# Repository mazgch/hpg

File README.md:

#  mazg.ch - HPG Solution

>**Note** This is a private project from [@mazgch](https://github.com/mazgch) <br> This code and hardware was developped during my free time. [u-blox](https://www.u-blox.com) decided to launch a simliar, inspired product under the name [XPLR-HPG-2](https://www.u-blox.com/en/product/xplr-hpg-2) along with production grade software based on [ubxlib](https://github.com/u-blox/ubxlib). u-blox has published the [hardware](https://github.com/u-blox/XPLR-HPG-hardware) and [software](https://github.com/u-blox/XPLR-HPG-software) on the [u-blox github account](https://github.com/u-blox). You can easily recognize the u-blox productized version by its green PCB color and u-blox sticker and silk logo on the back of the PCB.<br>
<br>
The Arduino software of this project can be compiled for the XPLR-HPG-2/1 by adjusting the `HW_TARGET` defines to `UBLOX_XPLR_HPG2_C214` in the [`software\HW.h`](./software/HW.h) file and selecting the right module/board. 

This project has the goal to demonstrate a high precision positioning function. It uses a Global Navigation Satellite System (GNSS) L1/L2 receiver with Real Time Kinematic (RTK) and Inertial Measurement Unit (IMU) Sensor based Dead Reckoning (DR) function to determine its location. In order achieve its best accuracy the receiver needs a correction data stream. On this solution the correction data can be received from a satellite broadcast using a LBAND receiver or over IP connectivity using Wi-FI or LTE. While other systems typically use local reference stations as correction source that have to be setup a maintained, this system makes use of a continental wide commercial SSR service. The whole solution shared in this project consist of three parts: 

## The three elements of the HPG Solution 

| [**HPG Hardware**](./hardware) | [**HPG Software**](./software) | [**HPG Monitor Webpage**](./monitor) |
|----------|----------|---------|
|  |  |  |
| The HPG hardware has a GNSS and a LBAND receiver that are used to achieve cm-Level precision. A Wi-Fi/BT module and a LTE modem make sure that the board is always connected to the internet. A USB port is used for changing or connecting a powerful host. The CPU of the Wi-Fi/BT module can be programmed with the HPG Software. | The HPG software implements a captive portal for configuration and monitoring. The software operates autonomously, configures all the modules and handles the different correction data sources and provides its data to the RTK system. It can also record two logfiles to the SD card of the GNSS/LBAND and the LTE communication. | The online HPG Monitor webpage at [hpg.mazg.ch](http://hpg.mazg.ch) is a online tools that allows you visualize the data of the solution. You can plot graph, export data to Excel or other offline tools. Satellite information as well as a map overlay are even available. The different messages and commands can be analyzed in a console. A simpler version can be accessed in the captive portal directly. |  

## Getting started

To make this device work as intended you need some accessories like LTE and GNSS antennas, a mobile data plan and nano SIM card and a subscription to PointPerfect. Follow this sequence to get the device configured and setup, click on the image below for a short YouTube video on how to do some of these steps.

1. Insert a nano SIM card, the socket is a push/push socket so don't try to just pull the card out.
2. Optional: Insert a micro-SD card (FAT, max 32GB) if you like the device to record logfiles. 
3. Attach the two LTE antennas to the SMA ports located on the long edges. To avoid mechanical stress on the center pin, make sure you do not rotate the antenna itself but only the nut of the SMA connector. 
4. Connect a survey grade L1/L2/L5 GNSS and LBAND antenna to the SMA port on the small edge of the device and place the antenna in a location with very good and unobstructed visibility to the sky. This is important to allow reliable LBAND reception as well as avoid multipath errors on the GNSS measurements 
5. Connect a USB cable to a computer, this will turn the device on, and you will see various LEDS turn on. In addition, your computer will enumerate several USB devices and serial as well a modem ports will become available.  

6. Optional: if the [software](./software) is not yet programmed, follow the build instructions of the Arduino based software and load it to the device. 
7. In order to add the device to your local Wi-Fi connect your computer or mobile phone with the `hpg-XXXXXX` Wi-Fi network. You will be directed to a captive portal where you can then enter your networks Wi-Fi credentials. Make sure that the Wi-Fi network that you like to connect to is supporting 2.4GHz band. Once done the device will connect to your local network and get an IP. You may want to reset your device to force a fast reconnection.
8. After the device is connected, you can try to connect to it using its host name `hpg-XXXXXX`. The IP address of the device is also reported in the debug output on the console output CDC port at 115'200 baud. A third option is to use the device discovery of the [HPG Monitor](http://hpg.mazg.ch). Some networks do not allow communication between attached Wi-Fi clients so it may be better to connect the device to your computer or mobile in hotspot mode. 
9. After you have successfully connected your device, you need to configure the PointPerfect location device token that you can get from the Thingstream portal and set the possible correction sources to use. If you do not have a device profile, create one with following settings: ``Status = enabled, Auto Activate Devices = true, Hardware Code = mandatory`` Return existing device details if Hardware Code is in use. You can also set the SIM pin, but it is often easier to remove the SIM pin from your SIM card with a mobile phone first. Alternatively you can provide the ``u-centerConfig.json`` to the device.  
10. After that the device will provision the credentials using zero touch provisioning (ZTP) from the PointPerfect servers.
11. Now you are ready to Monitor the operation of the device using the console output on the CDC, using the Monitor webpage that is served directly by the device.

11. You can also access and find your hpg devices using the HPG Monitor webpage at [hpg.mazg.ch](http://hpa.mazg.ch) This webpage displays various status information, messages and can even plot graphs of parameter or satellite signal strenghs. A map overlay completes the functionality of the HPG Monitor. You can even export your data a text, in common file formats for offline tools.
12. You are now ready to start experimenting with this exciting technology and go outside and test RTK positioning in your use cases. The solution is suitable for a variety of applications from Lawn Mower, Heavy machine and Construction vehicles, Drones, Precision Agriculture, Cars and of course Mobile Robotics. 
13. To get best performance sure that the GNSS/LBAND antenna is well positioned and has good visibility to the sky!
14. So have fun and put this solution on your robot, [vehicle](docu/Vehicle.md), [scooter](docu/Scooter.md) or [lawn mower](docu/Mower.md) project. Feel free to connect with me even if it’s just to share the projects you are building using this exciting technology and solution.

## Quick Reference Card

## An all [u-blox](https://www.u-blox.com) solution

This solution is an attempt to design a 'full u-blox solution' using various products In particular the solution implements following hardware and services:

| u-blox Product / Service | Description |
|:--------------:|-----------------------|
| [NINA-W106](https://www.u-blox.com/en/product/nina-w10-series-open-cpu) | An ESP32 based WIFI and BT module with Open CPU that will host the application.     | 
| [LARA-R6001D](https://www.u-blox.com/en/product/lara-r6-series) | A LTE Cat 1 cellular modem with 2G / 3G fallback. |
| [ZED-F9R](https://www.u-blox.com/en/product/zed-f9r-module) | A GNSS Module with RTK, DR and L1/L2 multiband capability. |
| [NEO-D9S](https://www.u-blox.com/en/product/neo-d9s-series) | A LBAND receiver to get PointPerfect correction service. | 
| [ANN-MB](https://www.u-blox.com/en/product/ann-mb-series) | L1/L2 multi-band, high precision GNSS antenna (LBAND is not offically supported, it may work but there is a slight degradation depending on the frequency) | 
| [PointPerfect](https://www.u-blox.com/en/product/pointperfect) | A continental wide SSR correction service with coverage in Europe and North America. |
| [AssistNow](https://www.u-blox.com/en/product/assistnow) | A assisted GNSS services that allows to speed up the system start. |

The hardware allows different SKUs and can be assembled with alternative modules with compatible form-factors such as [SARA-R510S](https://www.u-blox.com/en/product/sara-r5-series), [LENA-R8001](https://www.u-blox.com/en/product/lena-r8-series), [ZED-F9P](https://www.u-blox.com/en/product/zed-f9p-module) or [NEO-D9C](https://www.u-blox.com/en/product/neo-d9c-series).

## Availability

As this is a private project, availability of real prototypes and hardware is pretty much limited to friends and colleagues. I am sharing here my work with the open source community with the goal that others can learn from it and collaborate. If you like to have a discussion or business interesst you can contact me with a DM.

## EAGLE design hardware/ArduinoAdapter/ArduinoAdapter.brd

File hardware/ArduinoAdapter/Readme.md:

# Arduino Adapter Board

This is an adapter for replacing the ArduSimple board in the [Open Mower project](https://github.com/ClemensElflein/OpenMower) by [Clemens Elflein](https://github.com/ClemensElflein/OpenMower/commits?author=ClemensElflein) with this project or a XPLR-HPG-2.

**Remarks**
- The Yellow marked pin headers are mounted on bottom side to provide connection to the Open Mower board.
- The Purple marked pin headers are mounted on top side and connect to the HPG board.
- All other pin header signals are not connected, but can be mounted for mechanical stability. 
- When powering the board in this way do not connect a battery as this is used to inject supply from the Open mower board.

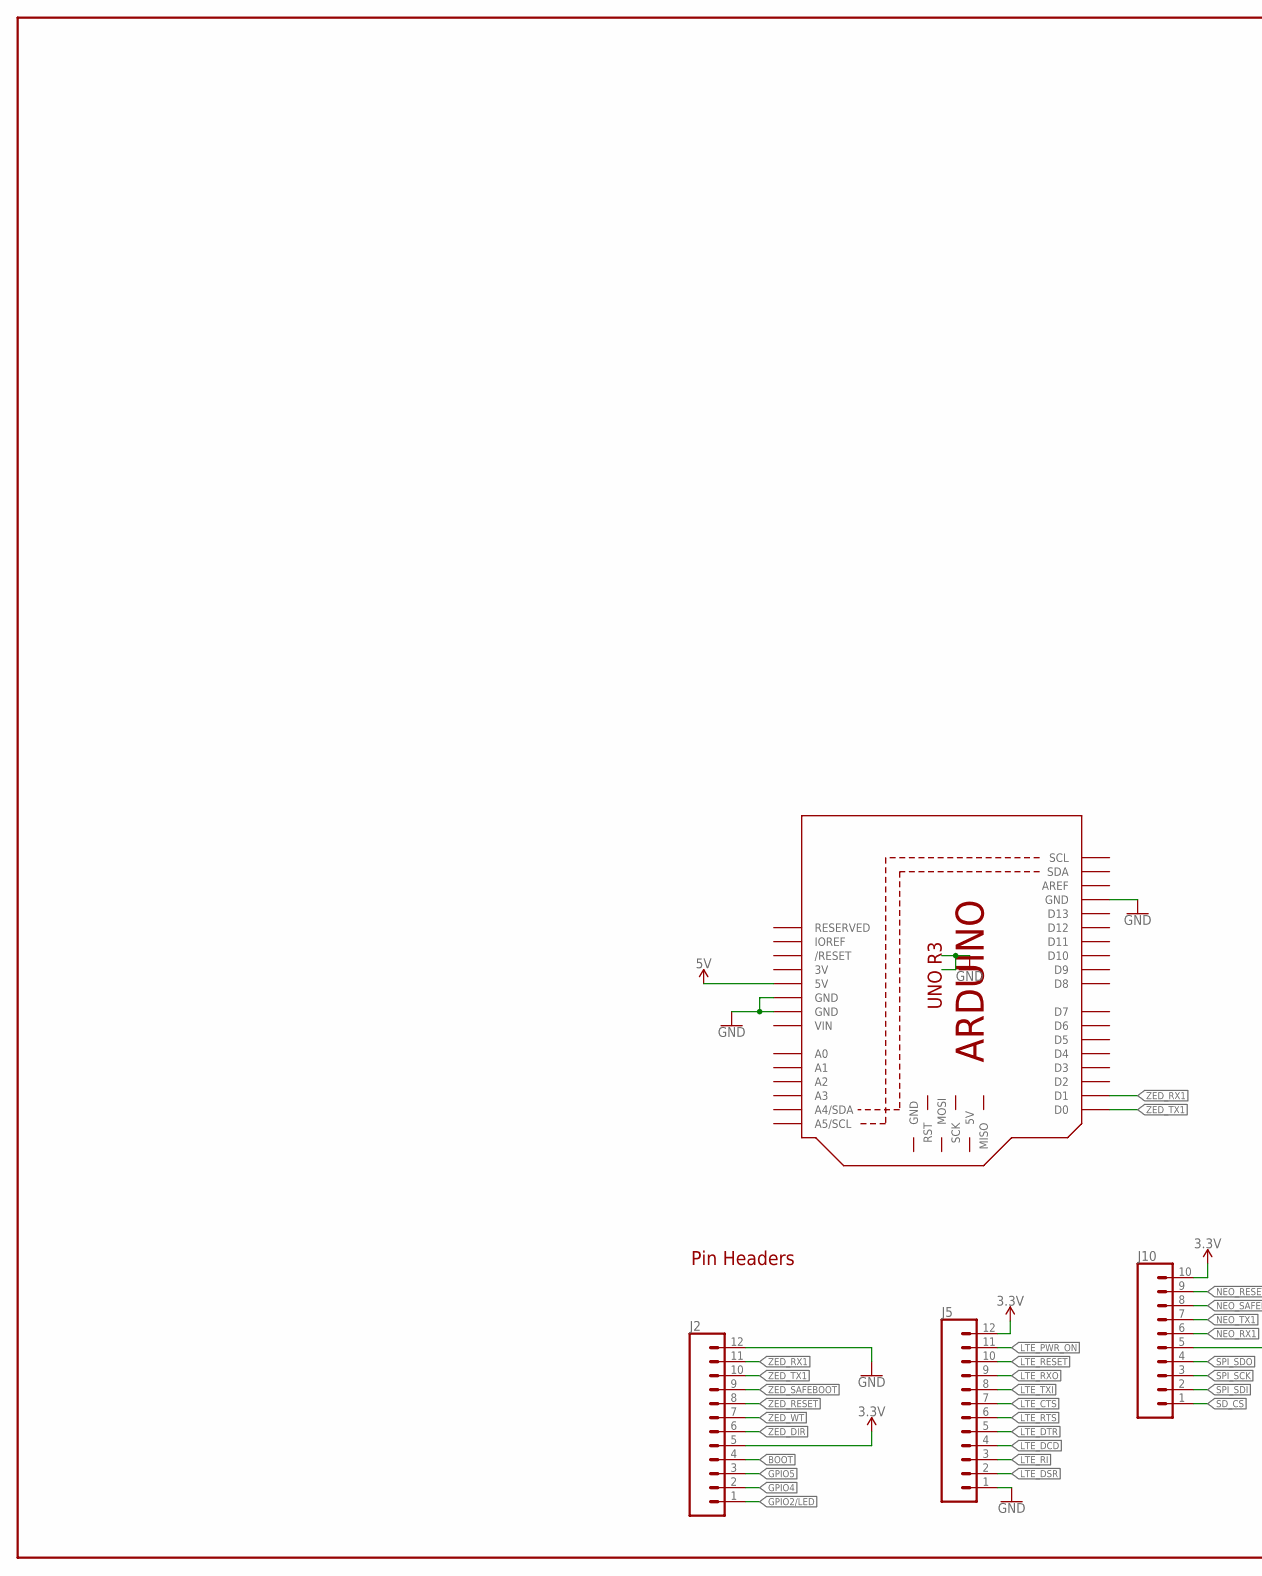
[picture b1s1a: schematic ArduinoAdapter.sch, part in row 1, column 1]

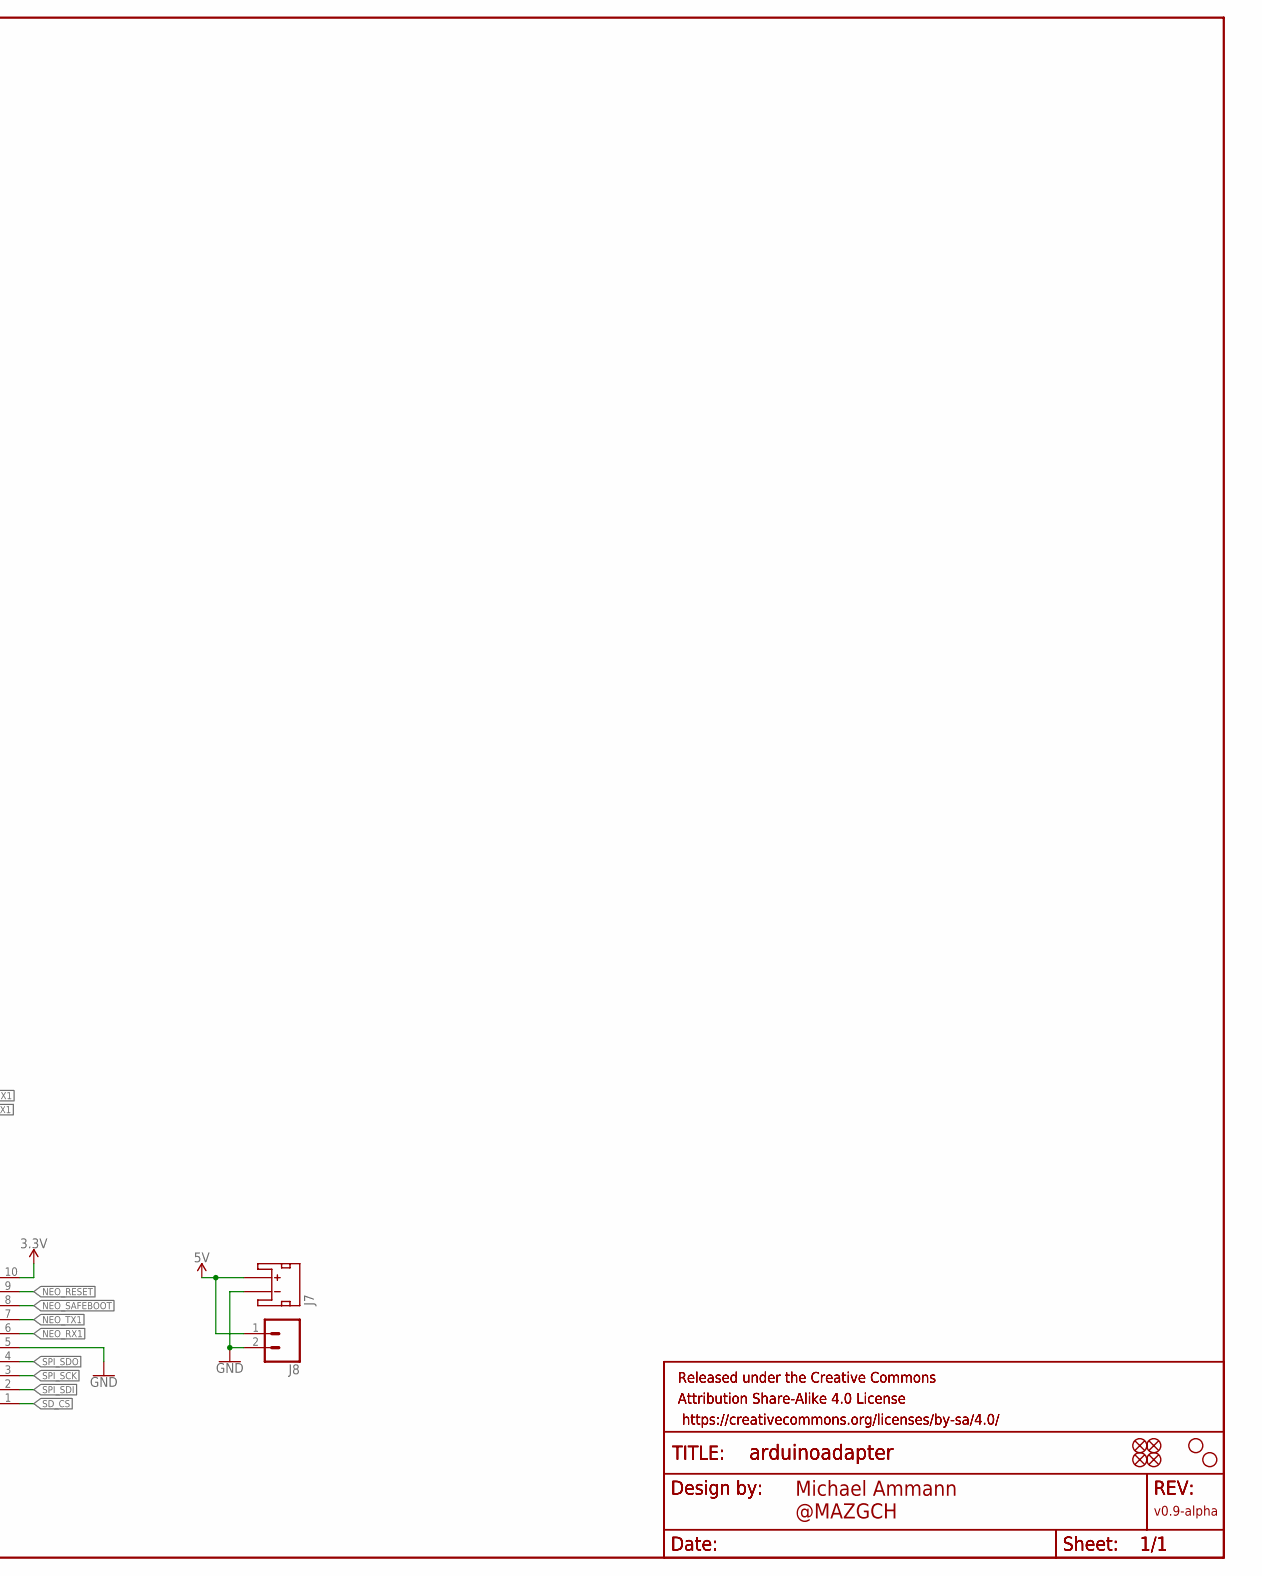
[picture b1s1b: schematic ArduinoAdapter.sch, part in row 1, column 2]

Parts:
FD1, FD2, FD3, FD4: FIDUCIALUFIDUCIAL; FIDUCIAL-MICRO
FRAME1, FRAME2: FRAME-LEDGER; CREATIVE_COMMONS
H1, H4: STAND-OFFTIGHT; STAND-OFF-TIGHT
J2, J5: CONN_12NO_SILK; 1X12_NO_SILK
J7: JST_2MM_MALE; JST-2-SMD
J8: CONN_021X02_NO_SILK; 1X02_NO_SILK
J10: CONN_10NO_SILK_PTH_FEMALE; 1X10_NO_SILK
M1: ARDUINO_R3_ICSP; ARDUINOR3_ICSP

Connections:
3.3V: J2.5, J5.12, J10.10
3V: M1.3V
5V: J7.2 (+), J8.1, M1.5V
!BOOT!: J2.4
GND: J2.12, J5.1, J7.1 (-), J8.2, J10.5, M1.GND, M1.GND@1 (GND), M1.GND@3 (GND)
GPIO2/LED: J2.1
GPIO4: J2.2
GPIO5: J2.3
LTE_!RESET!: J5.10
LTE_CTS: J5.7
LTE_DCD: J5.4
LTE_DSR: J5.2
LTE_DTR: J5.5
LTE_PWR_ON: J5.11
LTE_RI: J5.3
LTE_RTS: J5.6
LTE_RXO: J5.9
LTE_TXI: J5.8
NEO_!RESET!: J10.9
NEO_!SAFEBOOT!: J10.8
NEO_RX1: J10.6
NEO_TX1: J10.7
SD_!CS!: J10.1
SPI_SCK: J10.3
SPI_SDI: J10.2
SPI_SDO: J10.4
VIN: M1.VIN
ZED_!RESET!: J2.8
ZED_!SAFEBOOT!: J2.9
ZED_DIR: J2.6
ZED_RX1: J2.11, M1.D1
ZED_TX1: J2.10, M1.D0
ZED_WT: J2.7

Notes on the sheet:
Pin Headers
Michael Ammann @MAZGCH
v0.9-alpha

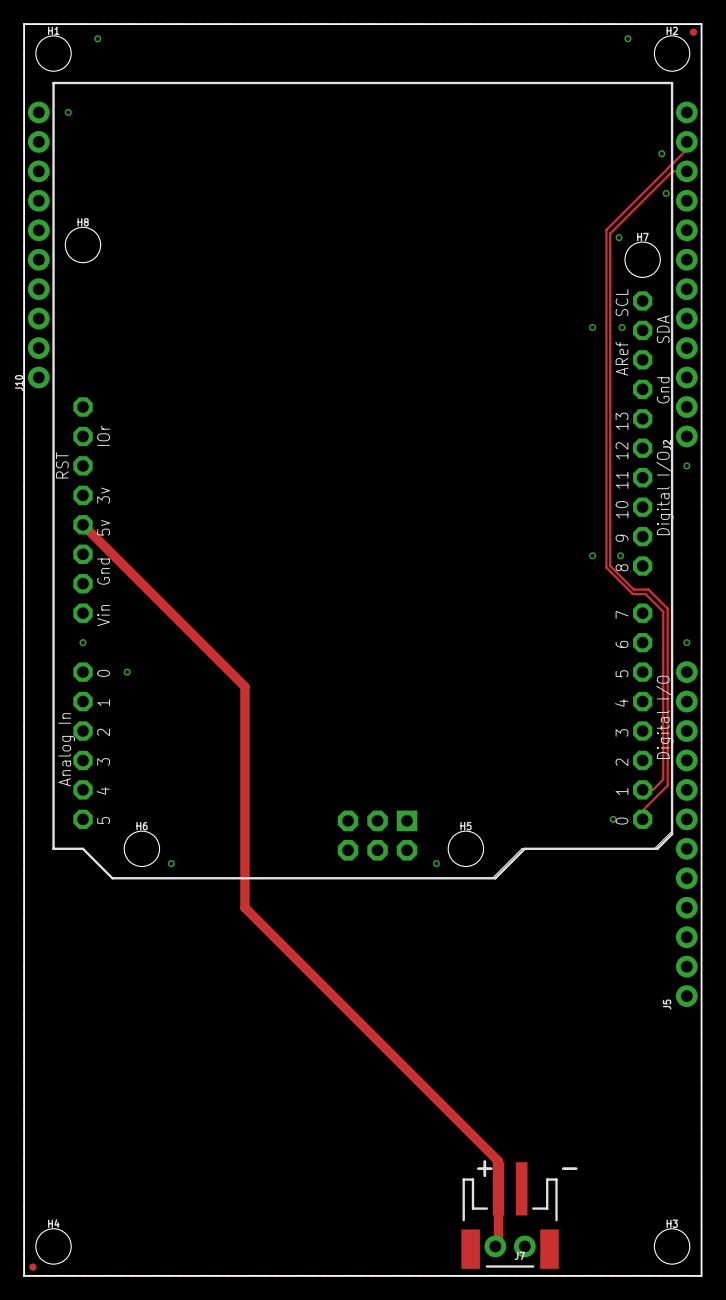
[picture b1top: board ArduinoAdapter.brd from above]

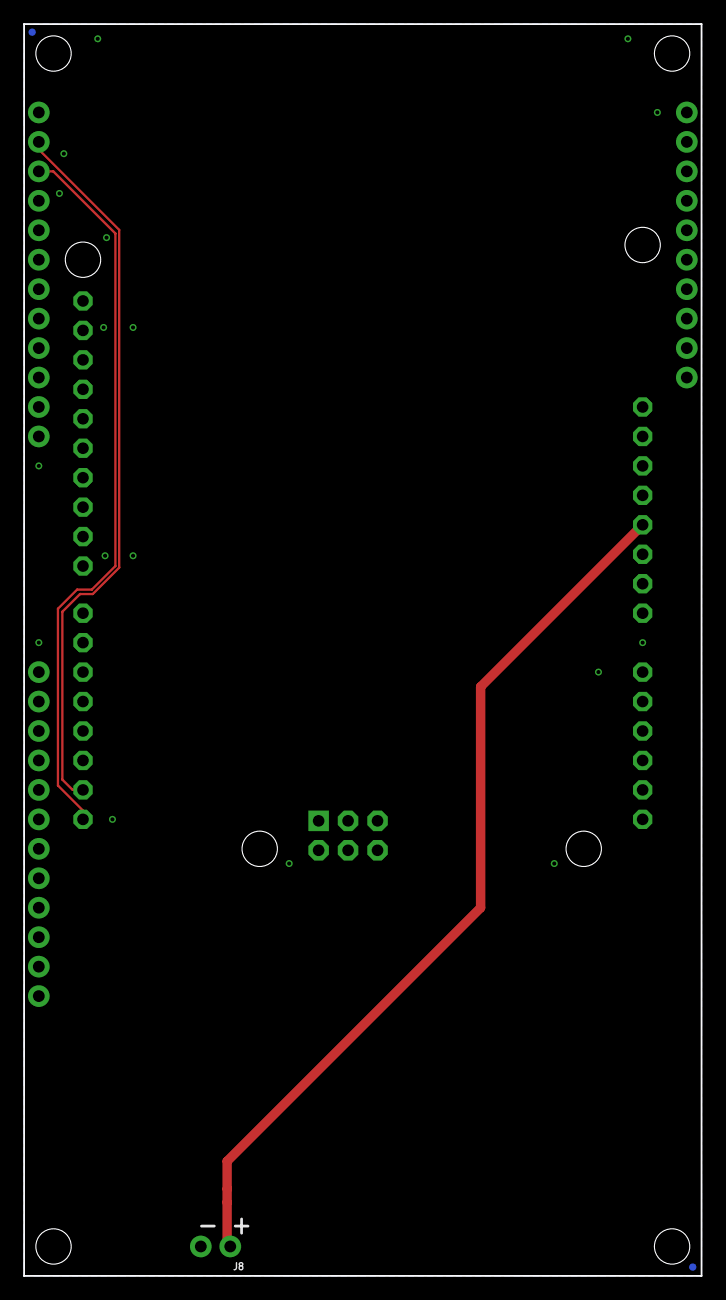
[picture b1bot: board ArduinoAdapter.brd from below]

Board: 2 copper layers, 58.4 x 108.0 mm, 20 parts (3 on the bottom side), 5 nets.

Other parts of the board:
H2, H3, H5, H6, H7, H8: STAND-OFFTIGHT; STAND-OFF-TIGHT

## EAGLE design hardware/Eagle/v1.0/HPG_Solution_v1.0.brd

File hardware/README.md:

# Hardware

This hardware was designed with Autodesk Eagle and is hugely based on Sparkfun open-source designs. The PCB is a standard four-layer PCB 1.6mm with quite conservative design rules and components, passives are mostly 0603. The core of the circuit is centered around various u-blox modules. The design's default assembly option are the following modules.

| u-blox Module                                                           | Function                                                     |
|:------------------------------------------------------------------------|:-------------------------------------------------------------|
| [NINA-W106](https://www.u-blox.com/en/product/nina-w10-series-open-cpu) | An ESP32 based WIFI and BT module with Open CPU that will host the application.     | 
| [LARA-R6001D](https://www.u-blox.com/en/product/lara-r6-series)         | A LTE Cat 1 cellular modem with 2G / 3G fallback.            |
| [ZED-F9R](https://www.u-blox.com/en/product/zed-f9r-module)             | A GNSS Module with RTK, DR and L1/L2 multiband capability.   |
| [NEO-D9S](https://www.u-blox.com/en/product/neo-d9s-series)             | A LBAND receiver to get PointPerfect correction service.     | 

## Design Resources 

Here you can find the schematic, layout and pictures of both sides of the PCB.
- [**PCB Schematic**](./HPG_Solution_sch.pdf)
- [**PCB Layout**](./HPG_Solution_brd.pdf)
- [**Autodesk Eagle Files**](./hardware/Eagle/)
- [**Gerber Files and Assembly Data**](./hardware/CAMOutputs)

&nbsp;

## LTE Modem 
There board was designed for u-blox [LARA-R6001D](https://www.u-blox.com/en/product/lara-r6-series) LTE modem, but it allows SKUs by swapping the cellular module to a  [SARA-R510](https://www.u-blox.com/en/product/sara-r5-series) for LTE Cat M1 NB-IoT or a [LENA-R8001](https://www.u-blox.com/en/product/lena-R8-series) Cat 1 bis. Several different modem variants are available from u-blox, only some BOM adjustments might be needed to make different SKUs of this function board. The board requires two external LTE antennas with SMA connectors (only one antenna would be used for [LENA-R8001](https://www.u-blox.com/en/product/lena-R8-series), [SARA-R510](https://www.u-blox.com/en/product/sara-r5-series). The LTE modem uses DCE notation and signal are connected straight to the NINA CPU (no null modem, crossover). The LTE_PWR_ON pin is also connected to a button to allow manual turning on of the LTE modem. The LTE_RESET pin unfortunately does not have a pull up resistor, this could be considered as a mistake, but it can be set by the NINA CPU after software is loaded. If this is not done, then the module will turn off after it booted  

| u-blox Series                                               | LTE Standard                         | # Antenna |
|:------------------------------------------------------------|:-------------------------------------|:---------:|
| [LARA-R6](https://www.u-blox.com/en/product/lara-r6-series) | LTE Cat 1 with 2G / 3G fallback      | 2         |
| [LENA-R8](https://www.u-blox.com/en/product/lena-R8-series) | LTE Cat 1bis with 2G / 3G fallback   | 1         |
| [SARA-R5](https://www.u-blox.com/en/product/sara-r5-series) | LTE Cat M1 / NB-IoT                  | 1         |
| [SARA-R4](https://www.u-blox.com/en/product/sara-r4-series) | LTE Cat M1 / NB-IoT with 2G fallback | 1         |

## High Precision GNSS and LBAND Receivers
The board was designed for u-blox **ZED-F9R** high precision GNSS RTK and DR module and a **NEO-D9S**, but it allows SKUs by swapping the modules to different variants such a **ZED-F9P** or the **NEO-D9C** that supports Japan's CLAS system. The board requires an external L1/L2/L5 and LBAND antenna with SMA connectors.

## Wi-Fi/BT with open CPU capability. 

NINA-W106-01 is a ESP32 with 8MB of FLASH memory. This module is responsible to run the software of the whole design. It can be easily programmed using different environments. The RESET and BOOT pins can be controlled with buttons and as well though a special Auto Reset circuit.

### NINA-W106 Pin Assignments

| GPIO  | Signal Function           | DIR | Comment                             |
|:-----:|:--------------------------|:---:|:------------------------------------|
|   0   | BOOT / GPIO0              | IN  | <- BOOT button, USB CDC RTS/CTS     |
|   1   | CDC_TX                    | OUT | -> USB CDC RX                       |
|   2   | LED / GPIO2               | OUT | -> LED                              |
|   3   | CDC_RX                    | IN  | -> USB CDC TX                       |
|   4   | GPIO4 / CAN_RX            | I/O | <- CAN (external)                   |
|   5   | GPIO5 / CAN_TX            | I/O | -> CAN (external)                   |
|  12   | LTE_PWR_ON                | OUT | active HIGH, **no pull up!**        |
|  13   | LTE_RESET                 | OUT | active LOW, ext pulled LOW          |
|  14   | LTE_DCD                   | OUT | -> LTE.                             |
|  15   | LTE_DTR                   | OUT | -> LTE                              |
|  18   | MICROSD_SCK / SCK         | OUT | -> SD card                          |
|  19   | MICROSD_SDI / COPI / MOSI | OUT | -> SD card                          |
|  23   | MICROSD_SDO / CIPO / MISO | IN  | <- SD card                          |
|  21   | I2C_SDA                   | I/O | <-> GNSS, LBAND, LTE, QWIC          |
|  22   | I2C_SCL                   | OUT | -> GNSS, LBAND, LTE, QWIC           |
|  25   | LTE_TXI                   | OUT | -> LTE                              |
|  26   | LTE_RXO                   | IN  | -> LTE                              |
|  27   | LTE_RTS                   | OUT | -> LTE                              |
|  32   | MICROSD_CS                | OUT | -> SD                               |
|  33   | VCC_EN                    | OUT | -> power supply                     |
|  34   | LTE_RI                    | IN  | <- LTE                              |
|  35   | VIN/3                     | IN  | <- power supply                     |
|  36   | LTE_CTS                   | IN  | <- LTE                              |
|  37   | LTE_ON                    | IN  | <- LTE                              |
|  38   | MICROSD_DET               | IN  | <- SD card holder                   |
|  39   | LTE_DSR                   | IN  | <- LTE                              |
| RESET | RESET                     | IN  | <- RESET button, USB CTS RTS/CTS    |

## Power Supply
The board has two 1A LDOs, one for the LTE modem and a second for all other functions. The status of the Power supply can be monitored using the different LEDs across the board. A changer is provided to support charging of a single 3.7V LIPO cell. A special LED will indicate the charging status. The **3.3V pins on the pin headers are output only** and can be used to power an external sensor or device like a CAN transceiver. 

## Other Functions

- **USB** The USB-C port provides as interface to an external host and is used for supplying the board. 
- **CAN** The GPIO4 and GPIO5 of the NINA-W106 can be used to connect a CAN transceiver such as a SN65HVD230. Thre a simple breakout board that you can attach using jumper wires such as the [CJMCU-230](https://de.aliexpress.com/item/32278648363.html)
- **BAT** A 3.7V single LIPO cell can be connected and will be charged when USB is connected. 
- **QWIK** The QWIK connector can be used to connect other I2C devices such as sensors or a display. 

## External Accessories

External antennas have to be connected to operate the device. The combined GNSS and LBAND antenna should support at least L1, L2 and LBAND frequency bands and it can support L5 band in addition. The antenna should be an antennna that is high precision capable, typically these are Helix type of antennas or active patch antennas with dual feed and reasonably sized GND planes (>10cm). If the antenna does not come with a ground plane, place it on a metal surface such as a car roof.
The LTE modem needs to 4G capable antennas and cover the band of the modem usually this is 700kHz - 2.6GHz. In addition you need to insert a SIM card with a data plan from your local mobile network operator.
A micro-SD card is only required if you intend to record logfiles from the modem of GNSS_ 

### Accessory parts and suppliers:
- Plexi were ordered from [Alibaba Shenzhen Elemei Display Products Co., Ltd](https://elemeidisplay.en.alibaba.com/minisiteentrance.html) they offer laser cut custom plexi under part number [OEM and ODM custom laser cut acrylic shapes customized service](https://www.alibaba.com/product-detail/OEM-and-ODM-custom-laser-cut_1600273363981.html) you send them the two PlexiTop and PlexBot layers exported as DXF file.  
- LTE antennas were ordered from [Advanced Aerial Store](https://de.aliexpress.com/store/912726145), you need 2pcs (= one order) of the following product for each board [2pcs/lot 4G Antenna 10dBi SMA Male 700-2700MHz for 4G LTE Router External Antenna](https://de.aliexpress.com/item/1005003688735673.html)
- The screws an nuts were ordered from [LANHAI Fastener Store](https://de.aliexpress.com/store/912262969), for a single board 4pcs are needed from each part. 
  - [M3x15mm / Phillips head screw](https://de.aliexpress.com/item/1005003106000201.html)
  - [hex nut M3](https://de.aliexpress.com/item/1005003106000201.html)
  - [Black / M3 ID3.1mm OD7mm / 3mm](https://de.aliexpress.com/item/1005003106036023.html)
  - [M3x6x1mm / black](https://de.aliexpress.com/item/1005003106227200.html)

## Known Issue of version 0.9: 
- The LTE_PWR_ON is floating towards GND, this causes the modem to constantly reset if no software is loaded. Software needs to be loaded that configures the GPIO12 either output HIGH or as INPUT with PULL-UP enabled. During reset the ESP applies however some LOW and high signal. It would be best to swap the LTE_RESET and LTE_PWRON pins to avoid changes during updates or reset. 
- The C41 was added to the Auto Reset circuit of the NINA-W106. This sometimes can cause issues with certain terminal applications or if the BOOT GPIO is used for other functions. Simply remove the C41 with a soldering iron if it causes issues for you.
- The shield of the SIM card holder is not connected to GND in the symbol. To make SIM detection work, we have to connect it to GND by makeing a solder bridge to GND pads of C38/36. In addition the software needs to set AT+UGPIOC=42,7 and AT+UDCONF=50,1. If SIM detection is not needed and then it is better to maybe remove R50. 
- On the v0.9 build some of the SIMhard holders are not porperly positioned on the board. This results in the component being a bit tilted due to the guidance pins. The parts were not repositioned but simply fixed with just more solder. 
- If special firmware is loaded to ZED-F9 (e.g., dev builds), make sure that RTK_STAT assigned to GPIO11 and GEOFENCE to GPIO12 to use that function.
- Higher baud rates on the LTE are not recommended even if RTS / CTS is used, this is a software issue and unrelated to hardware.
- LENA-R8: prototype require VCC of the module to be higher than 3.5V, this can be fixed by changing the dedicated LTE LDO to a adjustable version with a resistor divider at 3.8V. Also Pin 33 USB_BOOT of LENA should be routed to a jumper that can connect to VINT (V1.8) to allo firmware update over USB.
- Pins could be reassigned, to allow use of JTAG as alternative to the full 8 wire UART (second level shifter would need to be disabled.

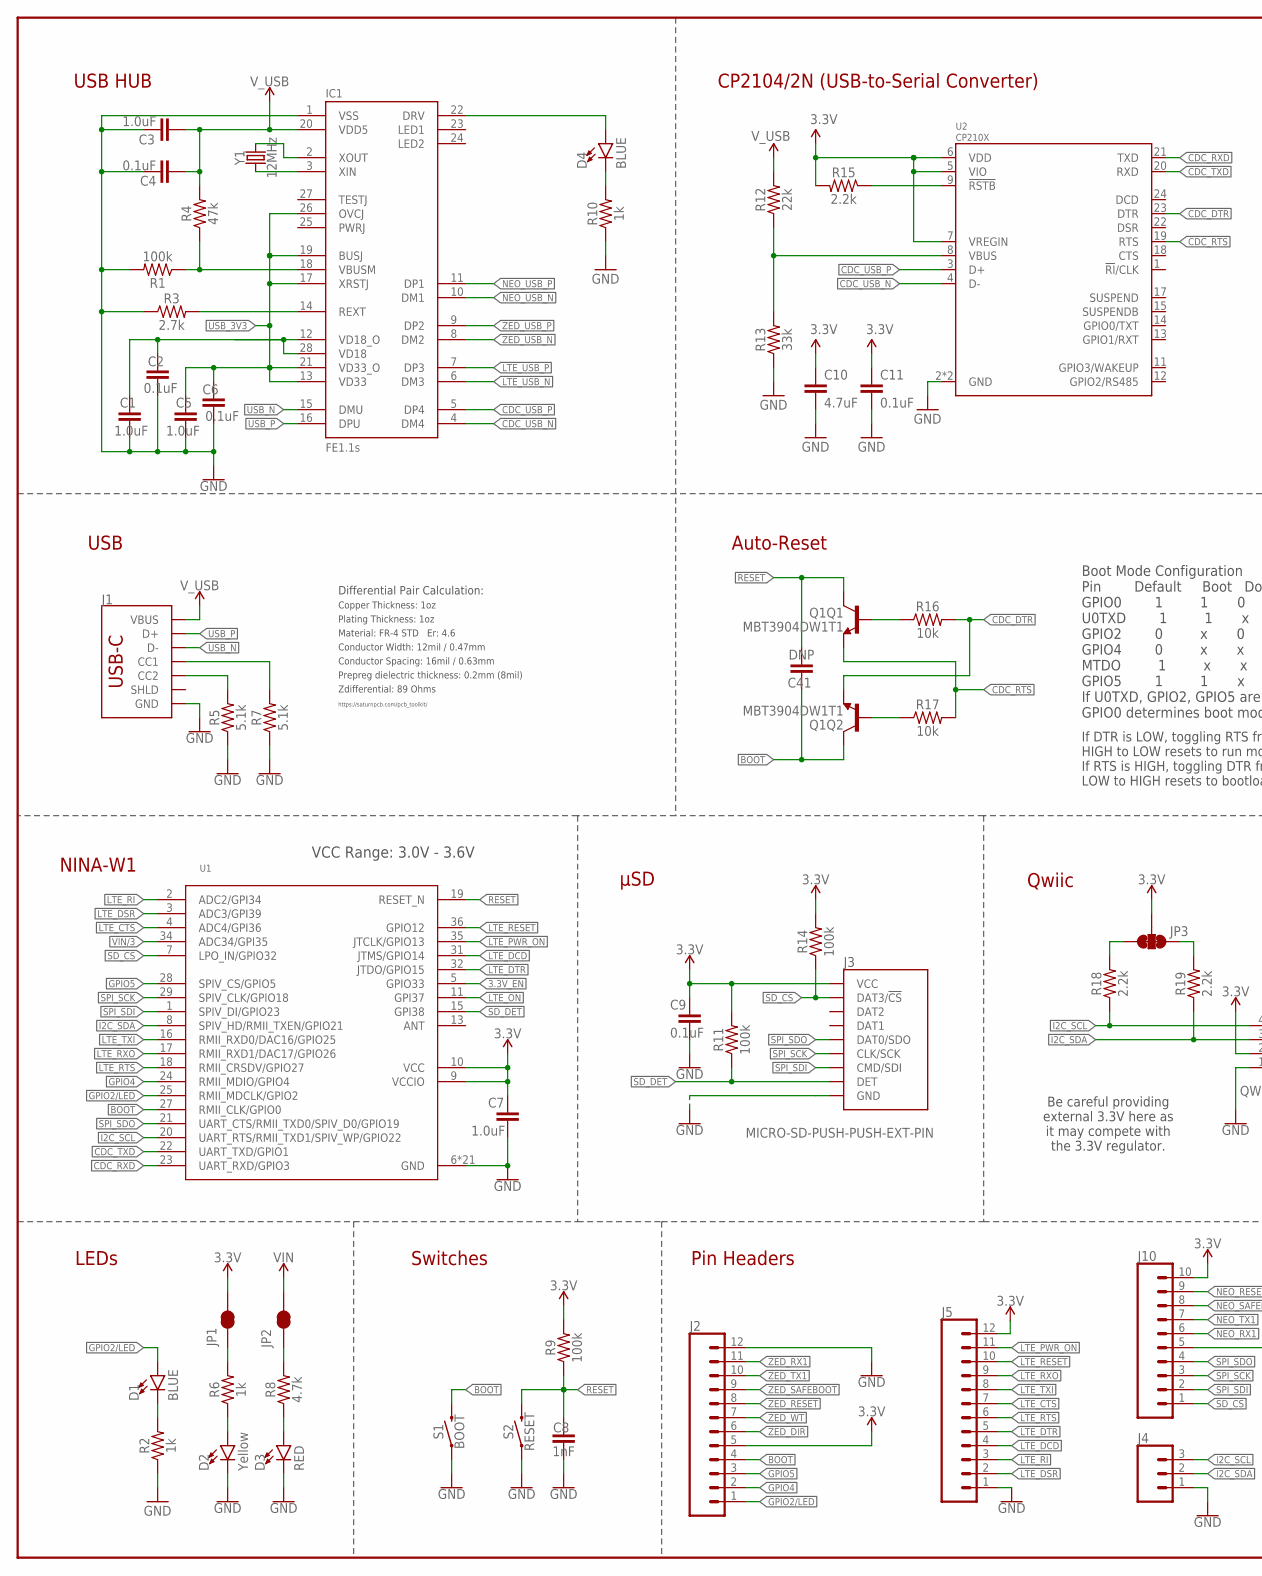
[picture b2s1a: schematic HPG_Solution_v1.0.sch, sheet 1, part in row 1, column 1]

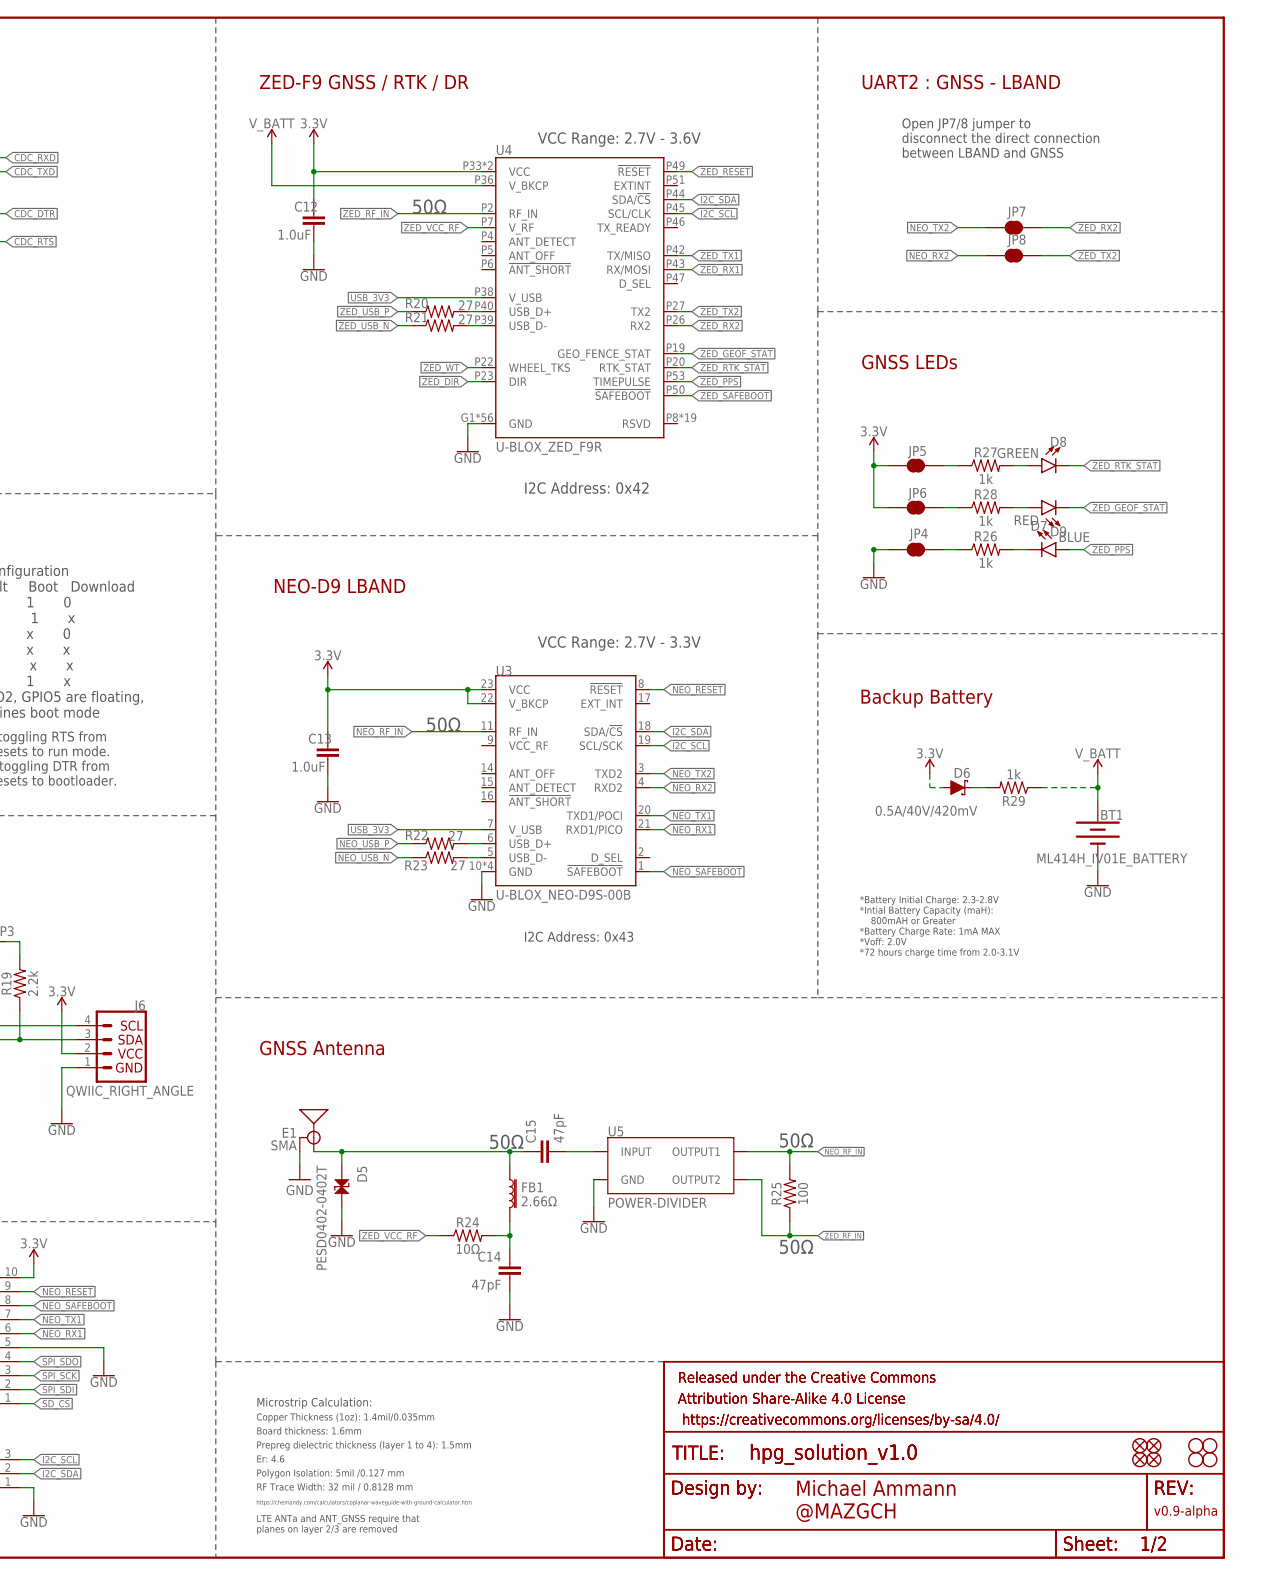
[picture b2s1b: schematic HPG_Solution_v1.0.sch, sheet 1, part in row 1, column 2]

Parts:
BT1: ML414H_IV01E_BATTERY; ML414H_IV01E
C1, C3, C5, C7, C12, C13: 1.0uF; 0603
C2, C4, C6, C9, C11: 0.1uF; 0603
C8: 1nF; 0603
C10: 4.7uF; 0603
C14, C15: 47pF; 0603
C41: DNP; 0603
D1, D4, D7: BLUE; LED-0603
D2: Yellow; LED-0603
D3, D9: RED; LED-0603
D5: PESD0402-0402T; 0402-TIGHT
D6: 0.5A/40V/420mV; SOD-323
D8: GREEN; LED-0603
E1: SMA; SMA-EDGE
FB1: 2.66Ω; 0402-TIGHT
FD1, FD2, FD3, FD4: FIDUCIALUFIDUCIAL; FIDUCIAL-MICRO
FRAME1, FRAME2: FRAME-LEDGER; CREATIVE_COMMONS
H1, H2, H3, H4: STAND-OFFTIGHT; STAND-OFF-TIGHT
IC1: FE1.1S; FE1.1S_SSOP-28
J1: USB_C_4-LAYER_PADS; USB-C-16P_4LAYER-PADS
J2, J5: CONN_12NO_SILK; 1X12_NO_SILK
J3: MICRO-SD-PUSH-PUSH-EXT-PIN; MICROSD-EXTERNALPIN
J4: CONN_031X03_NO_SILK; 1X03_NO_SILK
J6: QWIIC_RIGHT_ANGLE; JST04_1MM_RA
J10: CONN_10NO_SILK_PTH_FEMALE; 1X10_NO_SILK
JP1, JP2, JP4, JP5, JP6, JP7, JP8: JUMPER-SMT_2_NC_TRACE_SILK; SMT-JUMPER_2_NC_TRACE_SILK
JP3: JUMPER-SMT_3_2-NC_TRACE_SILK; SMT-JUMPER_3_2-NC_TRACE_SILK
Q1: MBT3904DW1T1; SC70-6
R1, R9, R11, R14: 100k; 0603
R2, R6, R10, R26, R27, R28, R29: 1k; 0603
R3: 2.7k; 0603
R4: 47k; 0603
R5, R7: 5.1k; 0603
R8: 4.7k; 0603
R12: 22k; 0603
R13: 33k; 0603
R15, R18, R19: 2.2k; 0603
R16, R17: 10k; 0603
R20, R21, R22, R23: 27; 0603
R24: 10Ω; 0402-TIGHT
R25: 100; 0603
S1: BOOT; TACTILE_SWITCH_SMD_5.2MM
S2: RESET; TACTILE_SWITCH_SMD_5.2MM
U1: NINA-W106NINA-W106; NINA-W106
U2: CP210X; QFN24
U3: U-BLOX_NEO-D9S-00B; NEO-M9N/M8T/M8U/D9S
U4: U-BLOX_ZED_F9R; UBLOX_ZED_F9R
U5: POWER-DIVIDER; PD0922J5050S2HF_ANA
Y1: 12MHz; CRYSTAL-SMD-5X3.2-4PAD

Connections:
3.3V: C7.1, C9.1, C10.1, C11.1, C12.1, C13.1, D6.A, J2.5, J3.4 (VCC), J5.12, J6.2, J10.10, JP1.2, JP3.2, JP5.1, JP6.1, R9.2, R11.2, R14.2, R15.2, U1.9 (VCCIO), U1.10 (VCC), U2.5 (VIO), U2.6 (VDD), U2.7 (VREGIN), U3.22 (V_BKCP), U3.23 (VCC), U4.P33 (VCC), U4.P34 (VCC); also elsewhere on the board
3.3V_EN: U1.5 (GPIO33); also elsewhere on the board
!BOOT!: C41.1, J2.4, Q1.6 (C), S1.3 (2), S1.4 (2), U1.27 (RMII_CLK/GPIO0)
!RESET!: C8.1, C41.2, Q1.3 (C), R9.1, S2.3 (2), S2.4 (2), U1.19 (RESET_N)
CDC_DTR: Q1.1 (E), R16.2, U2.23 (DTR)
CDC_RTS: Q1.4 (E), R17.2, U2.19 (RTS)
CDC_RXD: U1.23 (UART_RXD/GPIO3), U2.21 (TXD)
CDC_TXD: U1.22 (UART_TXD/GPIO1), U2.20 (RXD)
CDC_USB_N: IC1.4 (DM4), U2.4 (D-)
CDC_USB_P: IC1.5 (DP4), U2.3 (D+)
GND: BT1.-, C1.2, C2.2, C3.1, C4.1, C5.2, C6.2, C7.2, C8.2, C9.2, C10.2, C11.2, C12.2, C13.2, C14.2, D2.C, D3.C, D5.2, E1.GND@0 (GND), E1.GND@1 (GND), E1.GND@2 (GND), E1.GND@3 (GND), IC1.1 (VSS), J1.GND, J1.GND2 (GND), J2.12, J3.6 (GND), J3.10 (GND), J3.11 (GND), J3.12 (GND), J3.13 (GND), J4.1, J5.1, J6.1, J10.5, JP4.1, R1.2, R2.1, R3.1, R5.1, R7.1, R10.1, R13.1, S1.1, S1.2 (1), S2.1, S2.2 (1), U1.6 (GND), U1.12 (GND), U1.14 (GND), U1.26 (GND), U1.30 (GND), U1.GND@1 (GND), U1.GND@2 (GND), U1.GND@3 (GND), U1.GND@4 (GND), U1.GND@5 (GND), U1.GND@6 (GND), U1.GND@7 (GND), U1.GND@8 (GND), U1.GND@9 (GND), U1.GND@10 (GND), U1.GND@11 (GND), U1.GND@12 (GND), U1.GND@13 (GND), U1.GND@14 (GND), U1.GND@15 (GND), U1.GND@16 (GND), U2.2 (GND), U2.PAD (GND), U3.10 (GND), U3.12 (GND), U3.13 (GND), U3.24 (GND), U4.G1 (GND), U4.G2 (GND), U4.G3 (GND), U4.G4 (GND), U4.G5 (GND), U4.G6 (GND), U4.G7 (GND), U4.G8 (GND), U4.G9 (GND), U4.G10 (GND), U4.G11 (GND), U4.G12 (GND), U4.G13 (GND), U4.G14 (GND), U4.G15 (GND), U4.G16 (GND), U4.G17 (GND), U4.G18 (GND), U4.G19 (GND), U4.G20 (GND), U4.G21 (GND), U4.G22 (GND), U4.G23 (GND), U4.G24 (GND), U4.G25 (GND), U4.G26 (GND), U4.G27 (GND), U4.G28 (GND), U4.G29 (GND), U4.G30 (GND), U4.G31 (GND), U4.G32 (GND), U4.G33 (GND), U4.G34 (GND), U4.G35 (GND), U4.G36 (GND), U4.G37 (GND), U4.G38 (GND), U4.G39 (GND), U4.G40 (GND), U4.G41 (GND), U4.G42 (GND), U4.G43 (GND), U4.G44 (GND), U4.G45 (GND), U4.G46 (GND), U4.G47 (GND), U4.G48 (GND), U4.P1 (GND), U4.P3 (GND), U4.P12 (GND), U4.P14 (GND), U4.P32 (GND), U4.P37 (GND), U4.P41 (GND), U4.P48 (GND), U5.1 (GND), U5.3 (GND), U5.5 (GND); also elsewhere on the board
GPIO2/LED: D1.A, J2.1, U1.25 (RMII_MDCLK/GPIO2)
GPIO4: J2.2, U1.24 (RMII_MDIO/GPIO4)
GPIO5: J2.3, U1.28 (SPIV_CS/GPIO5)
I2C_SCL: J4.3, J6.4, R18.1, U1.20 (UART_RTS/RMII_TXD1/SPIV_WP/GPIO22), U3.19 (SCL/SCK), U4.P45 (SCL/CLK); also elsewhere on the board
I2C_SDA: J4.2, J6.3, R19.1, U1.8 (SPIV_HD/RMII_TXEN/GPIO21), U3.18 (SDA/!CS!), U4.P44 (SDA/!CS!); also elsewhere on the board
LED1: D4.A, IC1.22 (DRV)
LTE_!ON!: U1.11 (GPI37); also elsewhere on the board
LTE_!RESET!: J5.10, U1.36 (GPIO12); also elsewhere on the board
LTE_CTS: J5.7, U1.4 (ADC4/GPI36); also elsewhere on the board
LTE_DCD: J5.4, U1.31 (JTMS/GPIO14); also elsewhere on the board
LTE_DSR: J5.2, U1.3 (ADC3/GPI39); also elsewhere on the board
LTE_DTR: J5.5, U1.32 (JTDO/GPIO15); also elsewhere on the board
LTE_PWR_ON: J5.11, U1.35 (JTCLK/GPIO13); also elsewhere on the board
LTE_RI: J5.3, U1.2 (ADC2/GPI34); also elsewhere on the board
LTE_RTS: J5.6, U1.18 (RMII_CRSDV/GPIO27); also elsewhere on the board
LTE_RXO: J5.9, U1.17 (RMII_RXD1/DAC17/GPIO26); also elsewhere on the board
LTE_TXI: J5.8, U1.16 (RMII_RXD0/DAC16/GPIO25); also elsewhere on the board
LTE_USB_N: IC1.6 (DM3); also elsewhere on the board
LTE_USB_P: IC1.7 (DP3); also elsewhere on the board
unnamed: JP2.1, R8.2
unnamed: R22.2, U3.6 (USB_D+)
unnamed: R23.2, U3.5 (USB_D-)
unnamed: JP1.1, R6.2
unnamed: D2.A, R6.1
unnamed: D3.A, R8.1
unnamed: JP3.3, R18.2
unnamed: J1.A5 (CC1), R7.2
unnamed: J1.B5 (CC2), R5.2
unnamed: D8.A, R27.2
unnamed: JP3.1, R19.2
unnamed: C15.2, U5.2 (INPUT)
unnamed: JP5.2, R27.1
unnamed: JP4.2, R26.1
unnamed: Q1.5 (B), R16.1
unnamed: Q1.2 (B), R17.1
unnamed: D1.C, R2.2
unnamed: D7.C, R26.2
unnamed: D9.A, R28.2
unnamed: C14.1, FB1.2, R24.2
unnamed: JP6.2, R28.1
unnamed: R12.1, R13.2, U2.8 (VBUS)
unnamed: D6.C, R29.2
unnamed: R21.2, U4.P39 (USB_D-)
unnamed: R15.1, U2.9 (!RSTB)
unnamed: R20.2, U4.P40 (USB_D+)
unnamed: C1.1, C2.1, IC1.12 (VD18_O), IC1.28 (VD18)
unnamed: IC1.14 (REXT), R3.2
unnamed: IC1.2 (XOUT), Y1.3 (2)
unnamed: IC1.3 (XIN), Y1.1
unnamed: D4.C, R10.2
unnamed: IC1.18 (VBUSM), R1.1, R4.1
NEO_!RESET!: J10.9, U3.8 (!RESET!)
NEO_!SAFEBOOT!: J10.8, U3.1 (!SAFEBOOT!)
NEO_RF_IN: R25.2, U3.11 (RF_IN), U5.4 (OUTPUT1)
NEO_RX1: J10.6, U3.21 (RXD1/PICO)
NEO_RX2: JP8.1, U3.4 (RXD2)
NEO_TX1: J10.7, U3.20 (TXD1/POCI)
NEO_TX2: JP7.1, U3.3 (TXD2)
NEO_USB_N: IC1.10 (DM1), R23.1
NEO_USB_P: IC1.11 (DP1), R22.1
RF_IN: C15.1, D5.1, E1.SIG (SIGNAL), FB1.1
SD_!CS!: J3.2 (DAT3/!CS!), J10.1, R14.1, U1.7 (LPO_IN/GPIO32)
SD_DET: J3.9 (DET), R11.1, U1.15 (GPI38)
SPI_SCK: J3.5 (CLK/SCK), J10.3, U1.29 (SPIV_CLK/GPIO18)
SPI_SDI: J3.3 (CMD/SDI), J10.2, U1.1 (SPIV_DI/GPIO23)
SPI_SDO: J3.7 (DAT0/SDO), J10.4, U1.21 (UART_CTS/RMII_TXD0/SPIV_D0/GPIO19)
USB_3V3: C5.1, C6.1, IC1.13 (VD33), IC1.17 (XRSTJ), IC1.19 (BUSJ), IC1.21 (VD33_O), IC1.26 (OVCJ), U3.7 (V_USB), U4.P38 (V_USB)
USB_N: IC1.15 (DMU), J1.A7 (D-), J1.B7 (D-)
USB_P: IC1.16 (DPU), J1.A6 (D+), J1.B6 (D+)
VIN: JP2.2; also elsewhere on the board
VIN/3: U1.34 (ADC34/GPI35); also elsewhere on the board
V_BATT: BT1.+, R29.1, U4.P36 (V_BKCP)
V_USB: C3.2, C4.2, IC1.20 (VDD5), J1.VBUS1 (VBUS), J1.VBUS2 (VBUS), R4.2, R12.2; also elsewhere on the board
ZED_!RESET!: J2.8, U4.P49 (!RESET!)
ZED_!SAFEBOOT!: J2.9, U4.P50 (!SAFEBOOT!)
ZED_DIR: J2.6, U4.P23 (DIR)
ZED_GEOF_STAT: D9.C, U4.P19 (GEO_FENCE_STAT)
ZED_PPS: D7.A, U4.P53 (TIMEPULSE)
ZED_RF_IN: R25.1, U4.P2 (RF_IN), U5.6 (OUTPUT2)
ZED_RTK_STAT: D8.C, U4.P20 (RTK_STAT)
ZED_RX1: J2.11, U4.P43 (RX/MOSI)
ZED_RX2: JP7.2, U4.P26 (RX2)
ZED_TX1: J2.10, U4.P42 (TX/MISO)
ZED_TX2: JP8.2, U4.P27 (TX2)
ZED_USB_N: IC1.8 (DM2), R21.1
ZED_USB_P: IC1.9 (DP2), R20.1
ZED_VCC_RF: R24.1, U4.P7 (V_RF)
ZED_WT: J2.7, U4.P22 (WHEEL_TKS)

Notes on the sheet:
μSD
USB HUB
Pin Headers
Be careful providing external 3.3V here as it may compete with the 3.3V regulator.
Qwiic
LEDs
Switches
Plating Thickness: 1oz
Material: FR-4 STD Er: 4.6
Copper Thickness: 1oz
Conductor Spacing: 16mil / 0.63mm
Conductor Width: 12mil / 0.47mm
Prepreg dielectric thickness: 0.2mm (8mil)
https://saturnpcb.com/pcb_toolkit/
Differential Pair Calculation:
Zdifferential: 89 Ohms
Boot Mode Configuration Pin Default Boot Download GPIO0 1 1 0 U0TXD 1 1 x GPIO2 0 x 0 GPIO4 0 x x MTDO 1 x x GPIO5 1 1 x If U0TXD, GPIO2, GPIO5 are floating, GPIO0 determines boot mode
Auto-Reset
If DTR is LOW, toggling RTS from HIGH to LOW resets to run mode. If RTS is HIGH, toggling DTR from LOW to HIGH resets to bootloader.
CP2104/2N (USB-to-Serial Converter)
Backup Battery
*Battery Initial Charge: 2.3-2.8V *Intial Battery Capacity (maH): 800mAH or Greater *Battery Charge Rate: 1mA MAX *Voff: 2.0V *72 hours charge time from 2.0-3.1V
USB
NINA-W1
Michael Ammann @MAZGCH
I2C Address: 0x43
VCC Range: 2.7V - 3.3V
NEO-D9 LBAND
VCC Range: 2.7V - 3.6V
I2C Address: 0x42
ZED-F9 GNSS / RTK / DR
Open JP7/8 jumper to disconnect the direct connection between LBAND and GNSS
UART2 : GNSS - LBAND
Board thickness: 1.6mm
Er: 4.6
Copper Thickness (1oz): 1.4mil/0.035mm
RF Trace Width: 32 mil / 0.8128 mm
Polygon Isolation: 5mil /0.127 mm
Prepreg dielectric thickness (layer 1 to 4): 1.5mm
https://chemandy.com/calculators/coplanar-waveguide-with-ground-calculator.htm

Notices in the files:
parts and their libraries:
SparkFun-Aesthetics: Licensing: Creative Commons ShareAlike 4.0 International - https://creativecommons.org/licenses/by-sa/4.0
SparkFun-Aesthetics: Released under the Creative Commons Attribution Share-Alike 4.0 License
SparkFun-Aesthetics: https://creativecommons.org/licenses/by-sa/4.0
